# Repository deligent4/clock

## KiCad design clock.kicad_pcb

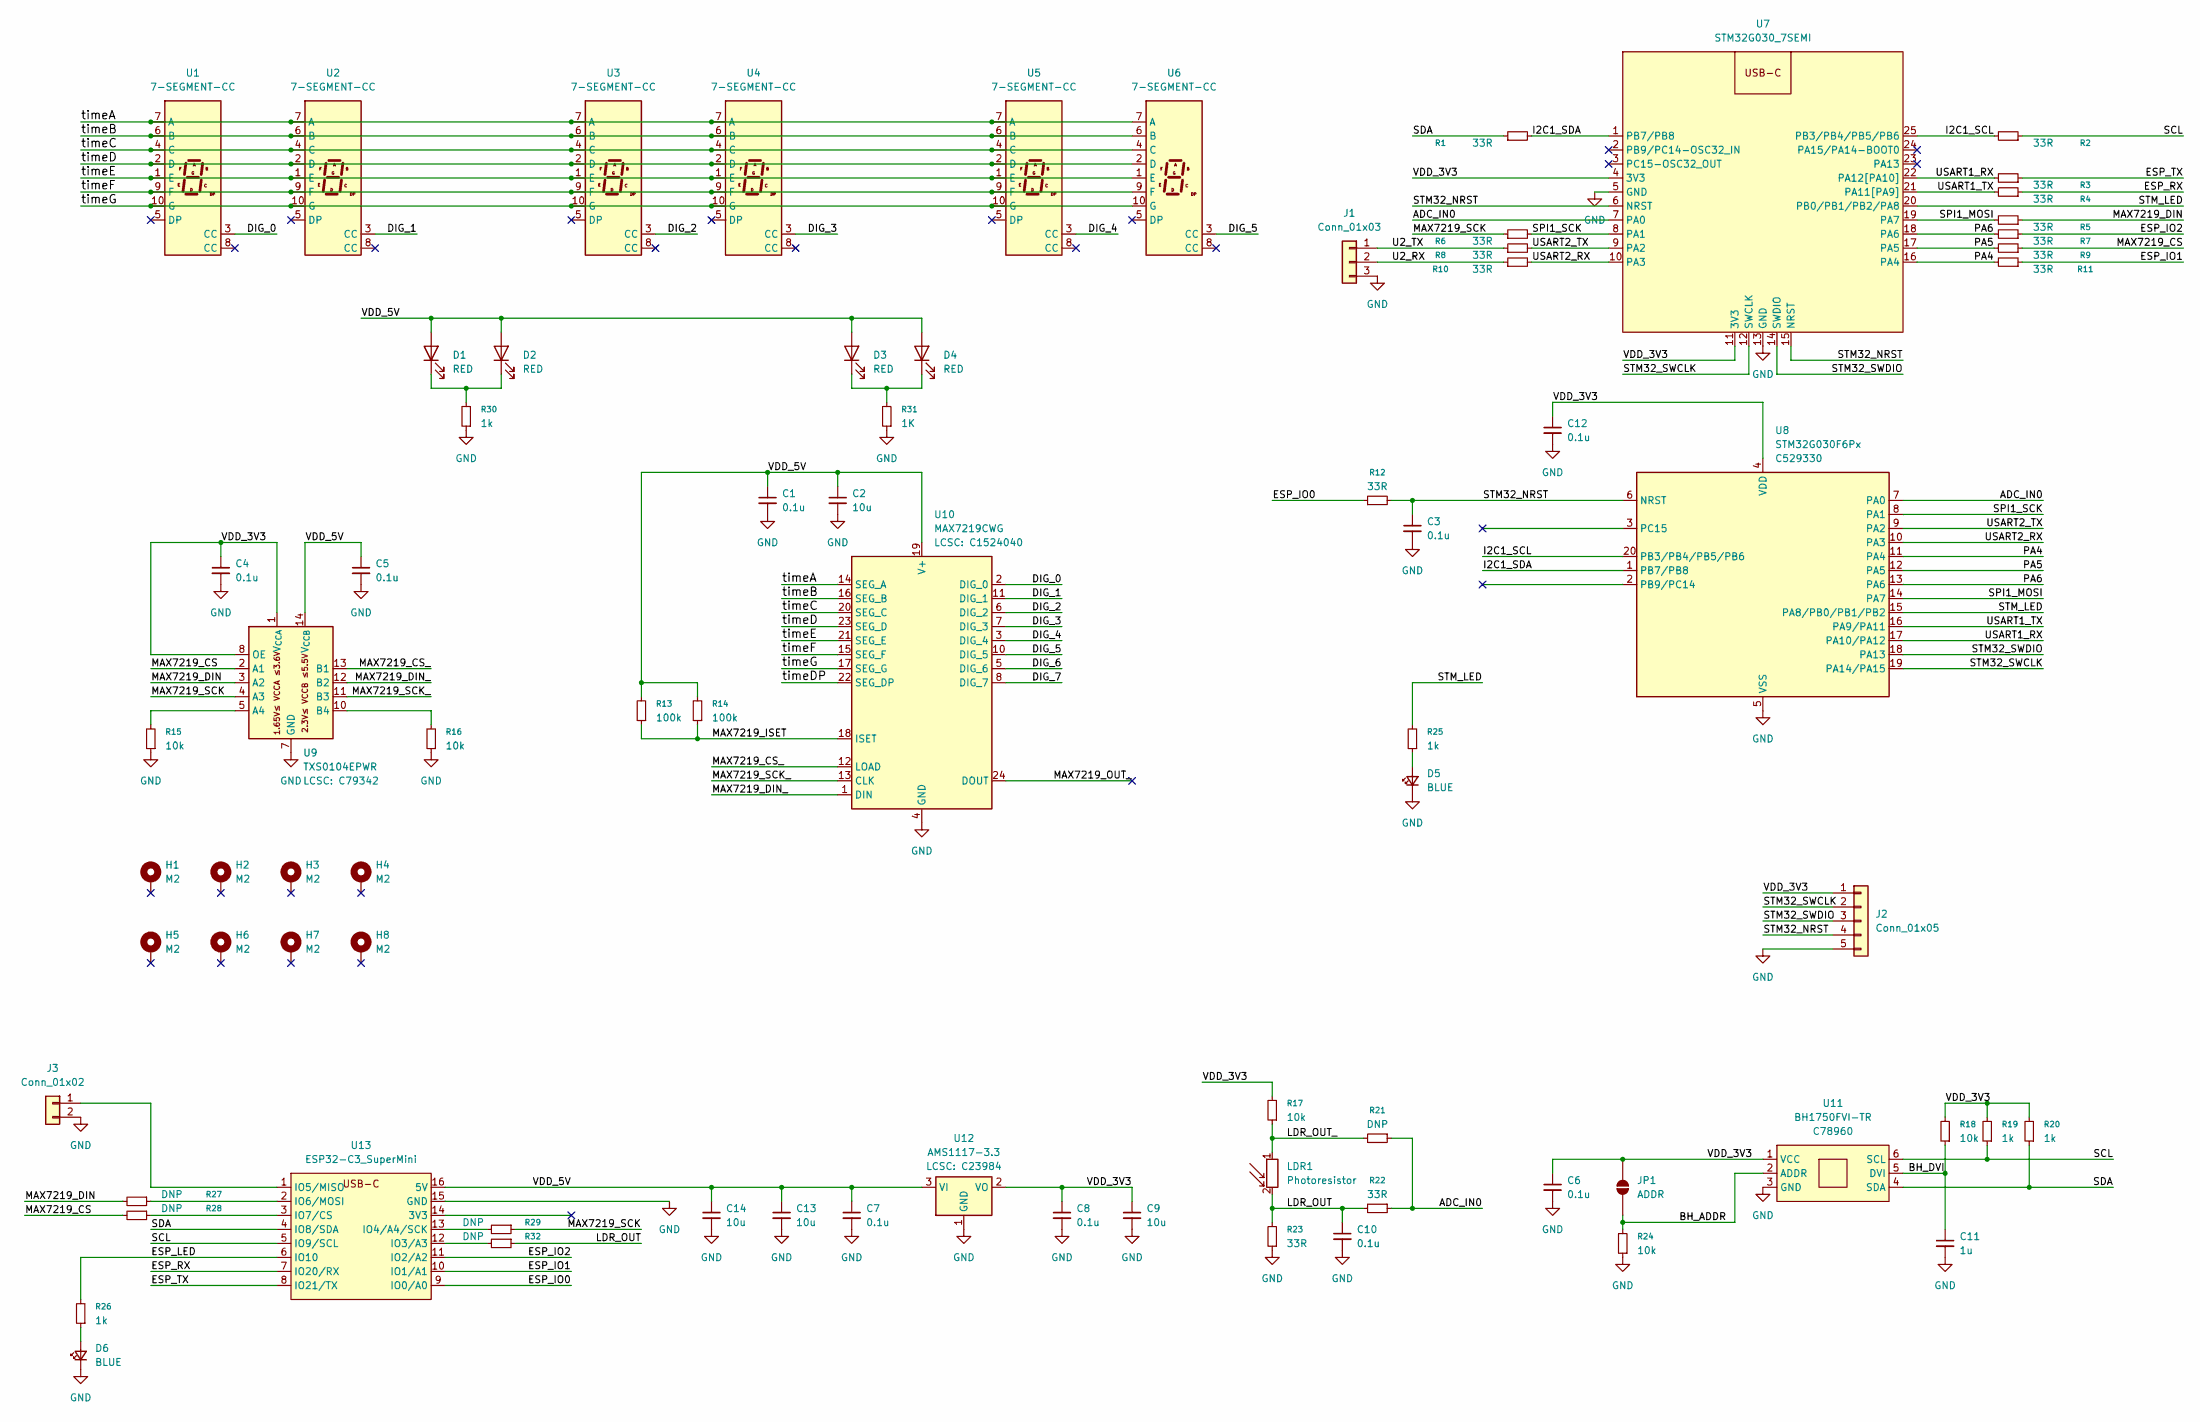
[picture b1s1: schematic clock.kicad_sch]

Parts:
C1, C3, C4, C5, C6, C7, C8, C10, C12: 0.1u; C_0603_1608Metric
C2, C9, C13, C14: 10u; C_0603_1608Metric
C11: 1u; C_0603_1608Metric
D1, D2, D3, D4: RED; LED_D3.0mm
D5, D6: BLUE; D_0603_1608Metric
H1, H2, H3, H4, H5, H6, H7, H8: M2; MountingHole_2.2mm_M2_DIN965_Pad
J1: Conn_01x03; PinHeader_1x03_P2.54mm_Vertical
J2: Conn_01x05; PinHeader_1x05_P2.54mm_Vertical
J3: Conn_01x02; PinHeader_1x02_P2.54mm_Vertical
JP1: ADDR; SolderJumper-2_P1.3mm_Open_RoundedPad1.0x1.5mm
LDR1: Photoresistor; R_LDR_5.0x4.1mm_P3mm_Vertical
R1, R2, R3, R4, R5, R6, R7, R8, R9, R10, R11, R12, R22, R23: 33R; R_0603_1608Metric
R13, R14: 100k; R_0603_1608Metric
R15, R16, R17, R18, R24: 10k; R_0603_1608Metric
R19, R20, R25, R26, R30: 1k; R_0603_1608Metric
R21, R27, R28, R29, R32: DNP; R_0603_1608Metric
R31: 1K; R_0603_1608Metric
U1, U2, U3, U4, U5, U6: 7-SEGMENT-CC; 7-SEGMENT-1-INCH
U7: STM32G030_7SEMI
U8: STM32G030F6Px; TSSOP-20_4.4x6.5mm_P0.65mm; LCSC C529330
U9: TXS0104EPWR; TSSOP-14_4.4x5mm_P0.65mm; LCSC C79342
U10: MAX7219CWG; SOIC-24W_7.5x15.4mm_P1.27mm; LCSC C1524040
U11: BH1750FVI-TR; WSOF6I-6_2.6x1.6mm_P0.5mm; LCSC C78960
U12: AMS1117-3.3; SOT-223-3_TabPin2; LCSC C23984
U13: ESP32-C3_SuperMini; ESP32-C3-SuperMini

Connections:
/ADC_IN0: R21.1, R22.1, U7.7 (PA0), U8.7 (PA0)
/BH_ADDR: JP1.1 (A), R24.2, U11.2 (ADDR)
/BH_DVI: C11.1, R18.1, U11.5 (DVI)
/DIG_0: U1.3 (CC), U10.2 (DIG_0)
/DIG_1: U2.3 (CC), U10.11 (DIG_1)
/DIG_2: U3.3 (CC), U10.6 (DIG_2)
/DIG_3: U4.3 (CC), U10.7 (DIG_3)
/DIG_4: U5.3 (CC), U10.3 (DIG_4)
/DIG_5: U6.3 (CC), U10.10 (DIG_5)
/DIG_6: U10.5 (DIG_6)
/DIG_7: U10.8 (DIG_7)
/ESP_IO0: R12.1, U13.9 (IO0/A0)
/ESP_IO1: R11.1, U13.10 (IO1/A1)
/ESP_IO2: R7.1, U13.11 (IO2/A2)
/ESP_LED: R26.2, U13.6 (IO10)
/ESP_RX: R4.1, U13.7 (IO20/RX)
/ESP_TX: R3.1, U13.8 (IO21/TX)
/I2C1_SCL: R2.2, U7.25 (PB3/PB4/PB5/PB6), U8.20 (PB3/PB4/PB5/PB6)
/I2C1_SDA: R1.2, U7.1 (PB7/PB8), U8.1 (PB7/PB8)
/LDR_OUT: C10.1, LDR1.2, R22.2, R23.2, R32.1
/LDR_OUT_: LDR1.1, R17.1, R21.2
/MAX7219_CS: R9.1, R28.2, U9.2 (A1)
/MAX7219_CS_: U9.13 (B1), U10.12 (LOAD)
/MAX7219_DIN: R5.1, R27.2, U9.3 (A2)
/MAX7219_DIN_: U9.12 (B2), U10.1 (DIN)
/MAX7219_ISET: R13.1, R14.1, U10.18 (ISET)
/MAX7219_OUT_: U10.24 (DOUT)
/MAX7219_SCK: R6.1, R29.1, U9.4 (A3)
/MAX7219_SCK_: U9.11 (B3), U10.13 (CLK)
/PA4: R11.2, U7.16 (PA4), U8.11 (PA4)
/PA5: R9.2, U7.17 (PA5), U8.12 (PA5)
/PA6: R7.2, U7.18 (PA6), U8.13 (PA6)
/SCL: R2.1, R19.1, U11.6 (SCL), U13.5 (IO9/SCL)
/SDA: R1.1, R20.1, U11.4 (SDA), U13.4 (IO8/SDA)
/SPI1_MOSI: R5.2, U7.19 (PA7), U8.14 (PA7)
/SPI1_SCK: R6.2, U7.8 (PA1), U8.8 (PA1)
/STM32_NRST: C3.1, J2.4, R12.2, U7.6 (NRST), U7.15 (NRST), U8.6 (NRST)
/STM32_SWCLK: J2.2, U7.12 (SWCLK), U8.19 (PA14/PA15)
/STM32_SWDIO: J2.3, U7.14 (SWDIO), U8.18 (PA13)
/STM_LED: R25.2, U7.20 (PB0/PB1/PB2/PA8), U8.15 (PA8/PB0/PB1/PB2)
/U2_RX: J1.2, R10.1
/U2_TX: J1.1, R8.1
/USART1_RX: R3.2, U7.22 (PA12[PA10]), U8.17 (PA10/PA12)
/USART1_TX: R4.2, U7.21 (PA11[PA9]), U8.16 (PA9/PA11)
/USART2_RX: R10.2, U7.10 (PA3), U8.10 (PA3)
/USART2_TX: R8.2, U7.9 (PA2), U8.9 (PA2)
/VDD_3V3: C4.1, C6.1, C8.1, C9.1, C12.1, J2.1, JP1.2 (B), R17.2, R18.2, R19.2, R20.2, U7.4 (3V3), U7.11 (3V3), U8.4 (VDD), U9.1 (V_{CCA}), U9.8 (OE), U11.1 (VCC), U12.2 (VO)
/VDD_5V: C1.1, C2.1, C5.1, C7.1, C13.1, C14.1, D1.2 (A), D2.2 (A), D3.2 (A), D4.2 (A), R13.2, R14.2, U9.14 (V_{CCB}), U10.19 (V+), U12.3 (VI), U13.16 (5V)
/timeA: U1.7 (A), U2.7 (A), U3.7 (A), U4.7 (A), U5.7 (A), U6.7 (A), U10.14 (SEG_A)
/timeB: U1.6 (B), U2.6 (B), U3.6 (B), U4.6 (B), U5.6 (B), U6.6 (B), U10.16 (SEG_B)
/timeC: U1.4 (C), U2.4 (C), U3.4 (C), U4.4 (C), U5.4 (C), U6.4 (C), U10.20 (SEG_C)
/timeD: U1.2 (D), U2.2 (D), U3.2 (D), U4.2 (D), U5.2 (D), U6.2 (D), U10.23 (SEG_D)
/timeDP: U10.22 (SEG_DP)
/timeE: U1.1 (E), U2.1 (E), U3.1 (E), U4.1 (E), U5.1 (E), U6.1 (E), U10.21 (SEG_E)
/timeF: U1.9 (F), U2.9 (F), U3.9 (F), U4.9 (F), U5.9 (F), U6.9 (F), U10.15 (SEG_F)
/timeG: U1.10 (G), U2.10 (G), U3.10 (G), U4.10 (G), U5.10 (G), U6.10 (G), U10.17 (SEG_G)
GND: C1.2, C2.2, C3.2, C4.2, C5.2, C6.2, C7.2, C8.2, C9.2, C10.2, C11.2, C12.2, C13.2, C14.2, D5.1 (K), D6.1 (K), J1.3, J2.5, J3.2, R15.1, R16.1, R23.1, R24.1, R30.1, R31.1, U7.5 (GND), U7.13 (GND), U8.5 (VSS), U9.7 (GND), U10.4 (GND), U10.9 (GND), U11.3 (GND), U12.1 (GND), U13.15 (GND)
unnamed: D1.1 (K), D2.1 (K), R30.2
unnamed: D3.1 (K), D4.1 (K), R31.2
unnamed: D5.2 (A), R25.1
unnamed: D6.2 (A), R26.1
unnamed: J3.1, U13.1 (IO5/MISO)
unnamed: R15.2, U9.5 (A4)
unnamed: R16.2, U9.10 (B4)
unnamed: R32.2, U13.12 (IO3/A3)
unnamed: R29.2, U13.13 (IO4/A4/SCK)
unnamed: R27.1, U13.2 (IO6/MOSI)
unnamed: R28.1, U13.3 (IO7/CS)

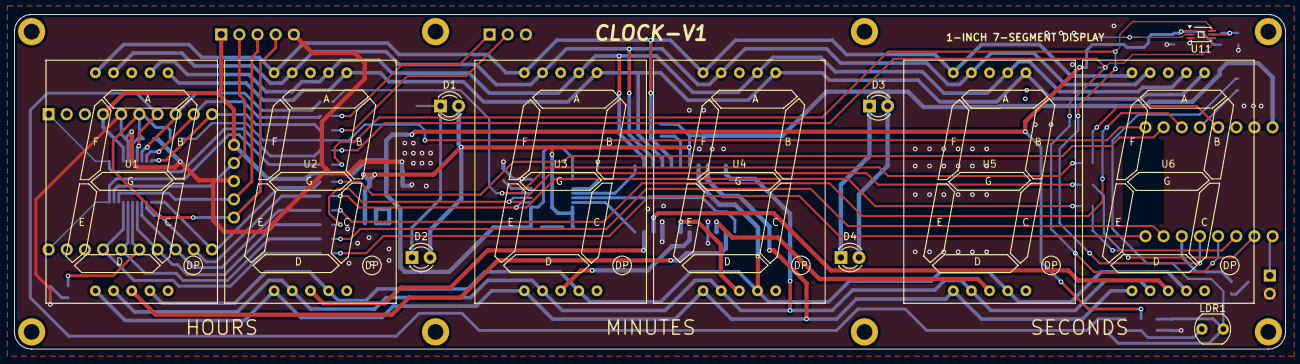
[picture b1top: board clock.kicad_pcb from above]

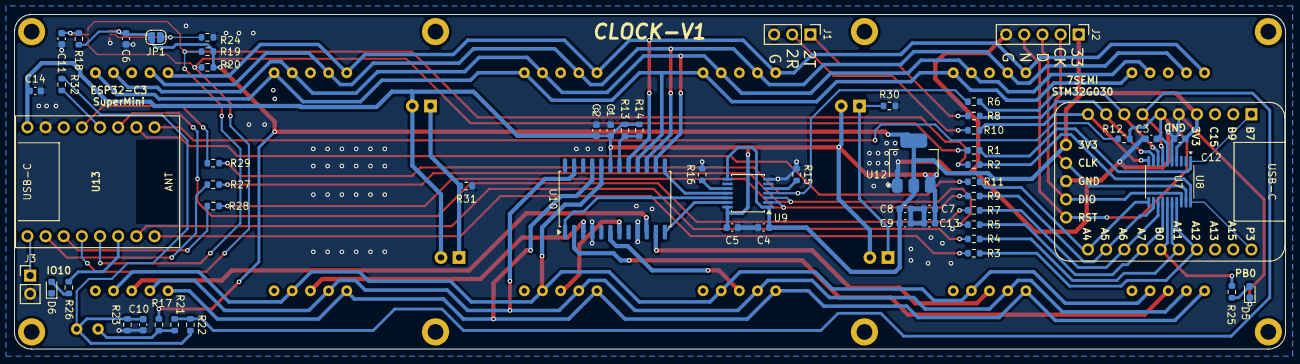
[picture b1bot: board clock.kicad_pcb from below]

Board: 2 copper layers, 177.8 x 46.8 mm, 78 parts (58 on the bottom side), 64 nets.

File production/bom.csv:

Designator,Footprint,Quantity,Value,LCSC Part #
"C1, C10, C12, C3, C4, C5, C6, C7, C8",0603,9,0.1u,
C11,0603,1,1u,
"C13, C14, C2, C9",0603,4,10u,
"D1, D2, D3, D4",LED_D3.0mm,4,RED,
"D5, D6",0603,2,BLUE,
J1,PinHeader_1x03_P2.54mm_Vertical,1,Conn_01x03,
J2,PinHeader_1x05_P2.54mm_Vertical,1,Conn_01x05,
J3,PinHeader_1x02_P2.54mm_Vertical,1,Conn_01x02,
LDR1,R_LDR_5.0x4.1mm_P3mm_Vertical,1,Photoresistor,
"R1, R10, R11, R12, R2, R22, R23, R3, R4, R5, R6, R7, R8, R9",0603,14,33R,
"R13, R14",0603,2,100k,
"R15, R16, R17, R18, R24",0603,5,10k,
"R19, R20, R25, R26, R30, R31",0603,6,1k,
"R21, R27, R28, R29, R32",0603,5,DNP,
"U1, U2, U3, U4, U5, U6",7-SEGMENT-1-INCH,6,7-SEGMENT-CC,
U10,SOIC-24W_7.5x15.4mm_P1.27mm,1,MAX7219CWG,C1524040
U11,WSOF6I-6_2.6x1.6mm_P0.5mm,1,BH1750FVI-TR,C78960
U12,SOT-223-3_TabPin2,1,AMS1117-3.3,C23984
U13,ESP32-C3-SuperMini,1,ESP32-C3_SuperMini,
U7,STM32G030_7SEMI,1,STM32G030_7SEMI,
U8,TSSOP-20_4.4x6.5mm_P0.65mm,1,STM32G030F6Px,C529330
U9,TSSOP-14_4.4x5mm_P0.65mm,1,TXS0104EPWR,C79342
